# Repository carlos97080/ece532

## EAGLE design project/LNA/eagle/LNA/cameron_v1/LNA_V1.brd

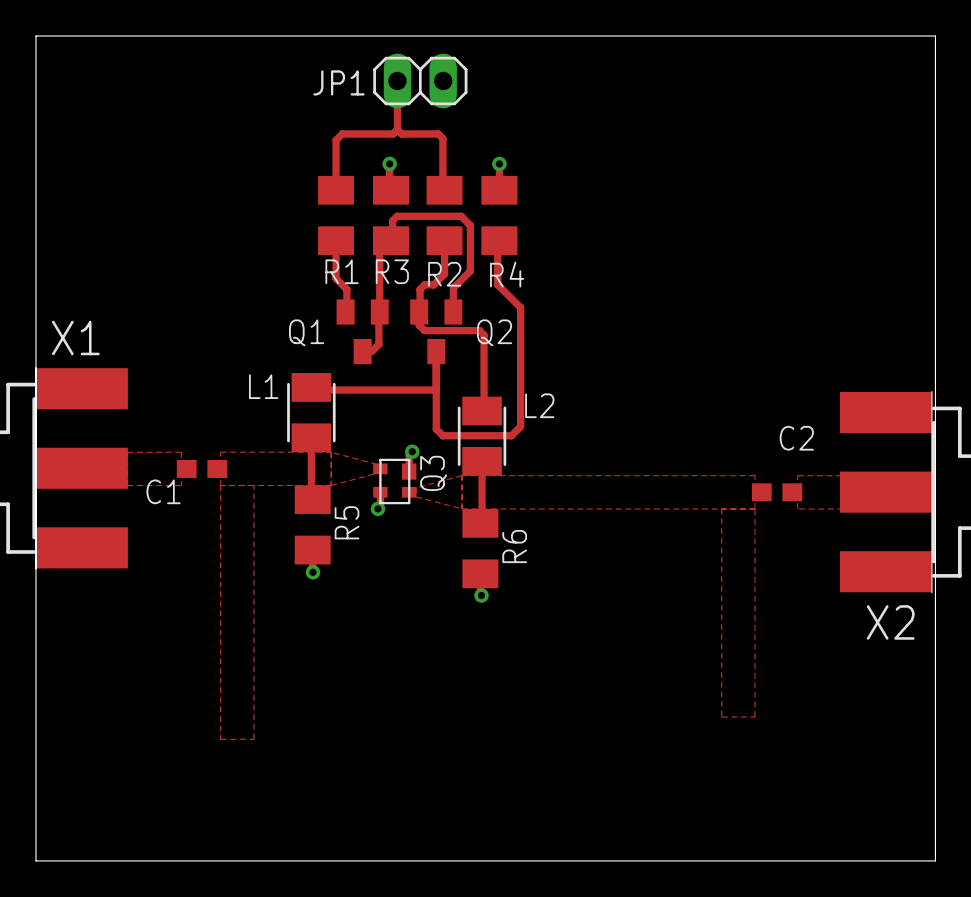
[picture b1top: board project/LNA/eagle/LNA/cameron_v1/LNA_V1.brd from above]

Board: 2 copper layers, 50.0 x 45.8 mm, 16 parts (0 on the bottom side), 10 nets.

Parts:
C1, C2: C0603
JP1: 1X02
L1, L2: 820nH; L3225M
Q1, Q2: MMBT3906LT1SMD; SOT23-BEC
Q3: SAV-541+; SOT-343
R1: 3k; M1206
R2: 15; M1206
R3, R4: 4320; M1206
R5: 50; M1206
R6: 100; M1206
X1, X2: SMA-142-0701-871/876; J502-ND-142-0701-871/876

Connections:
+3.3V: JP1.1, R1.2, R2.2
GND: JP1.2, Q3.2, Q3.4, R3.2, R4.2, R5.2, R6.2, X1.G@1, X1.G@2, X1.G@3, X1.G@4, X2.G@1, X2.G@2, X2.G@3, X2.G@4
INPUT: C1.1, L1.2, Q3.3, R5.1
ISO_INPUT: C1.2, X1.1
ISO_OUTPUT: C2.1, X2.1
unnamed: Q1.B, Q1.C, Q2.B, R3.1
unnamed: Q1.E, R1.1
OUTPUT: C2.2, L2.2, Q3.1, R6.1
VD: L2.1, Q2.E, R2.1
VG: L1.1, Q2.C, R4.1

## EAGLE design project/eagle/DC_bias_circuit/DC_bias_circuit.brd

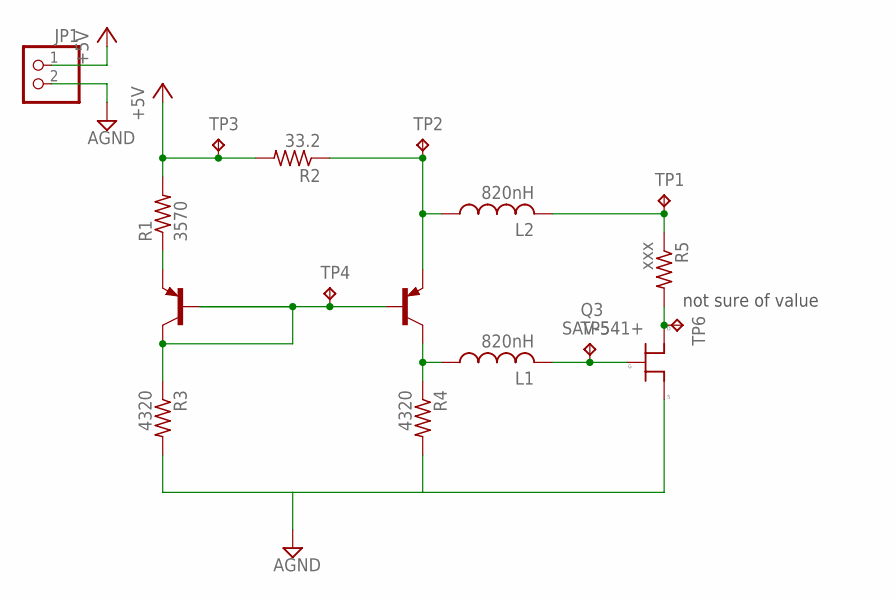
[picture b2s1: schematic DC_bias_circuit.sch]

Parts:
JP1: PINHD-1X2; 1X02
L1, L2: 820nH; L3225M
Q1, Q2: MMBT3906LT1SMD; SOT23-BEC
Q3: SAV-541+; SOT-343
R1: 3570; M1206
R2: 33.2; M1206
R3, R4: 4320; M1206
R5: xxx; M1206
TP1, TP2, TP3, TP4, TP5, TP6: TPB1,27; B1,27

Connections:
+5V: JP1.1, R1.2, R2.2, TP3.TP
DRAIN: Q3.1 (D), R5.2, TP6.TP
GATE: L1.2, Q3.3 (G), TP5.TP
GND: JP1.2, Q3.2 (S), Q3.4 (S), R3.2, R4.2
unnamed: Q1.B, Q1.C, Q2.B, R3.1, TP4.TP
unnamed: L1.1, Q2.C, R4.1
unnamed: Q1.E, R1.1
unnamed: L2.1, Q2.E, R2.1, TP2.TP
unnamed: L2.2, R5.1, TP1.TP

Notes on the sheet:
not sure of value

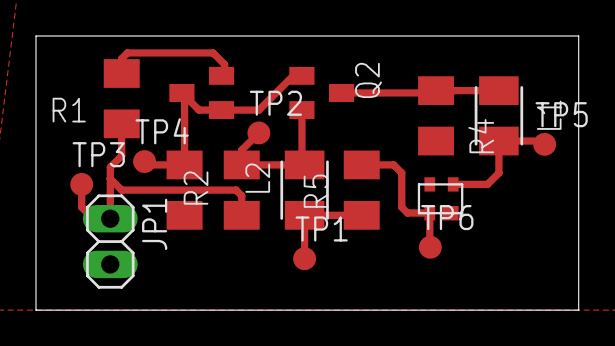
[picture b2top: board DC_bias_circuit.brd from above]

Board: 2 copper layers, 30.1 x 15.2 mm, 17 parts (0 on the bottom side), 9 nets.

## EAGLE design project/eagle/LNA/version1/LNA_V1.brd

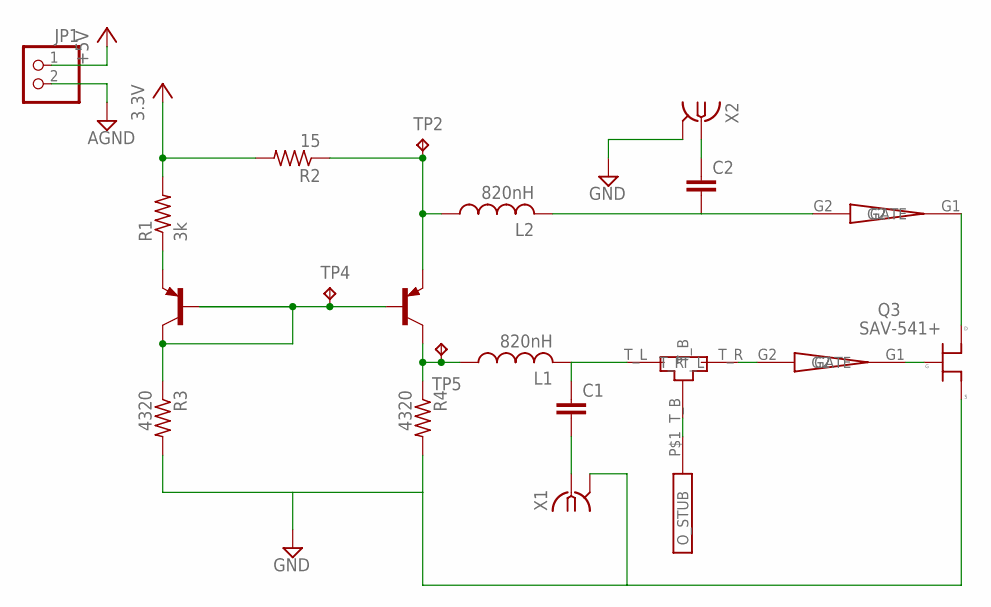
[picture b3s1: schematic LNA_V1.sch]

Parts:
C1, C2: C-EUC0603; C0603
JP1: PINHD-1X2; 1X02
L1, L2: 820nH; L3225M
Q1, Q2: MMBT3906LT1SMD; SOT23-BEC
Q3: SAV-541+; SOT-343
R1: 3k; M1206
R2: 15; M1206
R3, R4: 4320; M1206
TP2, TP4, TP5: TPB1,27; B1,27
U$1, U$4: TAPPERED_TL1
U$2: TEE_TL1
U$3: OPEN_STUB1
X1, X2: SMA-142-0701-871/876; J502-ND-142-0701-871/876

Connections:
+3.3V: JP1.1, R1.2, R2.2
GND: JP1.2, Q3.2 (S), Q3.4 (S), R3.2, R4.2, X1.G@1 (2), X1.G@2 (2), X1.G@3 (2), X1.G@4 (2), X2.G@1 (2), X2.G@2 (2), X2.G@3 (2), X2.G@4 (2)
unnamed: Q1.B, Q1.C, Q2.B, R3.1, TP4.TP
unnamed: L1.1, Q2.C, R4.1, TP5.TP
unnamed: Q3.3 (G), U$1.G1 (GATE)
unnamed: Q1.E, R1.1
unnamed: U$1.G2, U$2.T_R
unnamed: L2.1, Q2.E, R2.1, TP2.TP
unnamed: C1.1, L1.2, U$2.T_L
unnamed: U$2.T_B, U$3.P$1
unnamed: C1.2, X1.1
unnamed: C2.2, L2.2, U$4.G2
unnamed: C2.1, X2.1
unnamed: Q3.1 (D), U$4.G1 (GATE)

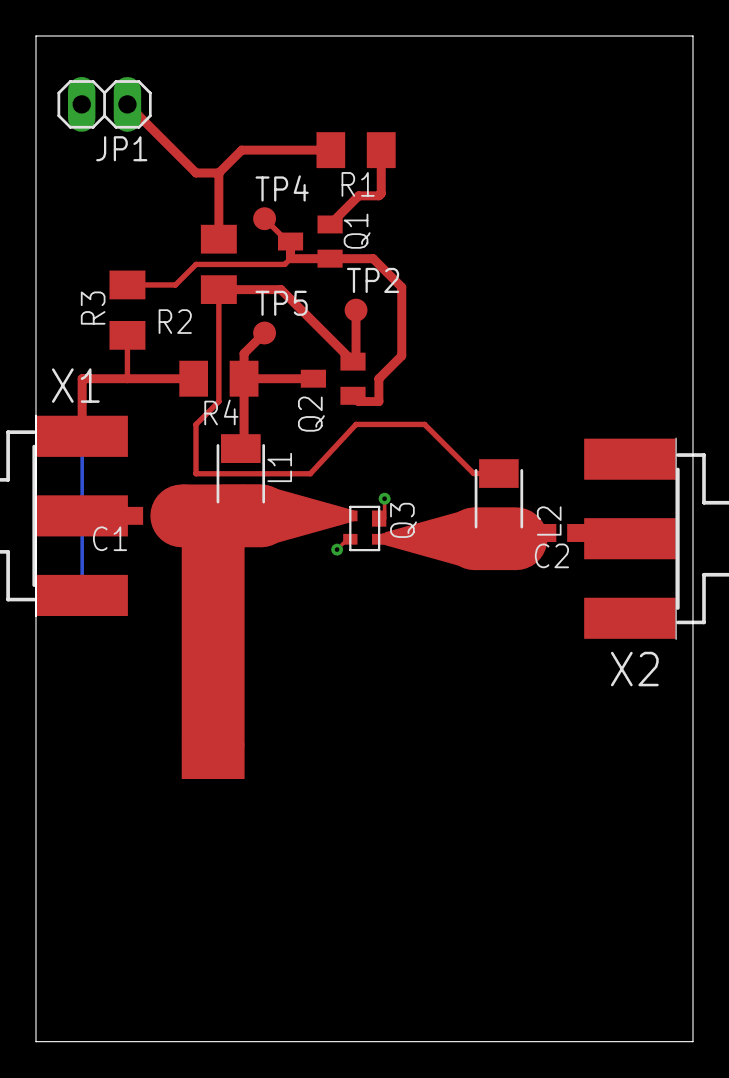
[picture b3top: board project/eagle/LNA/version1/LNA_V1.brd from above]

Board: 2 copper layers, 36.5 x 55.9 mm, 21 parts (0 on the bottom side), 14 nets.

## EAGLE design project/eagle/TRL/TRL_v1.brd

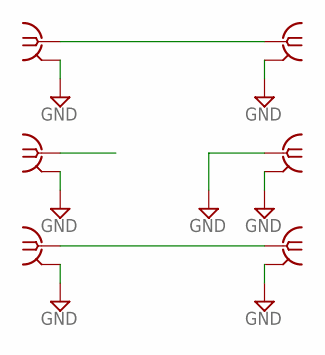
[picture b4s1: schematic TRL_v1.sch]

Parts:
X1, X2, X3, X4, X5, X6: SMA-142-0711-821/826; J502-ND-142-0711-821/826

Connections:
GND: X1.G@1 (2), X1.G@2 (2), X1.G@3 (2), X1.G@4 (2), X2.G@1 (2), X2.G@2 (2), X2.G@3 (2), X2.G@4 (2), X3.G@1 (2), X3.G@2 (2), X3.G@3 (2), X3.G@4 (2), X4.1, X4.G@1 (2), X4.G@2 (2), X4.G@3 (2), X4.G@4 (2), X5.G@1 (2), X5.G@2 (2), X5.G@3 (2), X5.G@4 (2), X6.G@1 (2), X6.G@2 (2), X6.G@3 (2), X6.G@4 (2)
OPEN: X3.1
QUARTER: X5.1, X6.1
THRU: X1.1, X2.1

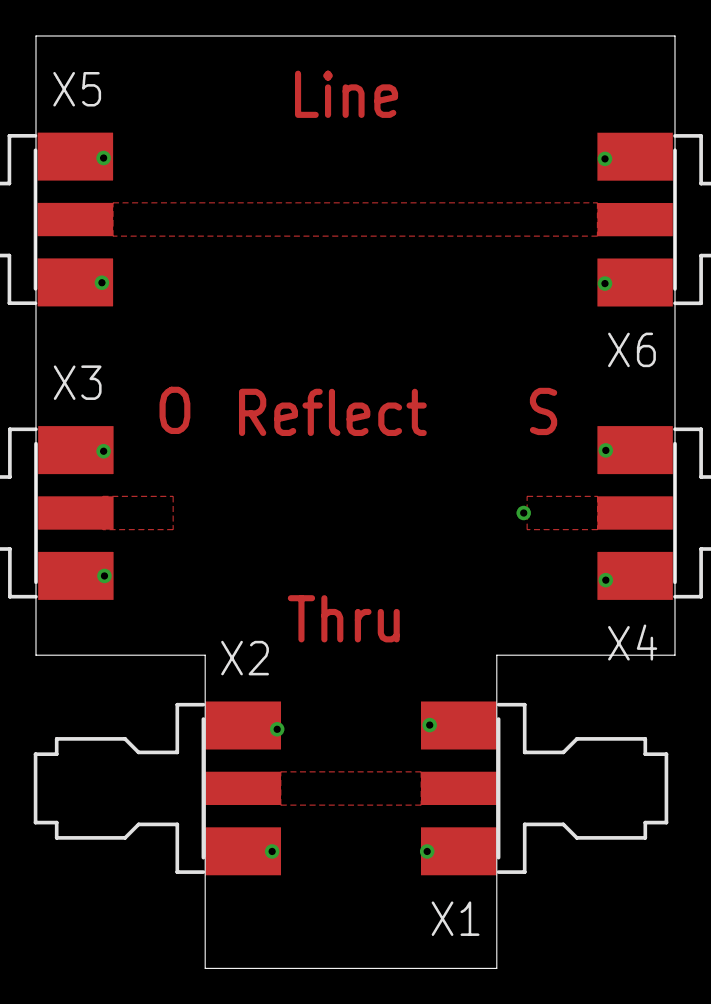
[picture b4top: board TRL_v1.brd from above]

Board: 2 copper layers, 35.5 x 51.8 mm, 6 parts (0 on the bottom side), 3 nets.
